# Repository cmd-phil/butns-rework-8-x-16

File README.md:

# Overview

128 button grid as a rework of jhbruhns 64 clone heavily based on previous work by [hugelton/btns](https://github.com/hugelton/Btns).

Uses a Rasperry Pi Pico Microcontroller, NeoPixel RGB LEDs (SK6812), cheap buttons and a 3d-printed case and button-overlay.
The tilt-sensor of the 8x8 version is not available: all usable GPIOs are needed for the 8x16 matrix.

## 16x8 specifics

| Item | Value |
|------|-------|
| PCB size | 190.44 mm x 99 mm, 2 layers |
| Rows `SW_ROW_1..8` | GPIO0..7 |
| Columns `SW_COL_1..7` | GPIO8..14 |
| Columns `SW_COL_8..15` | GPIO16, 17, 18, 19, 20, 21, 22, 26 |
| Column `SW_COL_16` | GPIO15 |
| LED data | GPIO28 via 74LVC1G17, one chain of 128 LEDs, row by row, 16 per row, starting top left |
| Free GPIO | GPIO27 |
| Mounting holes | 4 corners, 2 inner (M2.5) |

The firmware limits the estimated LED current to `MAX_LED_CURRENT_MA` (400 mA, see `firmware/src/firmware.cpp`).
One SK6812-EC20 draws up to 12 mA per colour channel plus about 1 mA idle, so 128 LEDs at full level exceed what a USB port and the 0.2 mm supply traces can deliver.
Hold the top-left key while plugging in for the default orientation, the bottom-right key for 180 degrees.

An alternative firmware in `firmware-iii/` runs monome iii Lua scripts with colour functions for the RGB LEDs and also has a monome serial mode. See `firmware-iii/README.md`.

Maximum LED brightness: hold the two top corner keys for one second. Then press any key, its column sets the maximum (column 1 = 1/16, column 16 = 100 %).
The selected column lights up at that brightness. The mode ends 3 seconds after the last key press and the value is stored in flash.
No key events are sent to the host while the mode is active.

# Building

It is highly recommended to order the PCB assembled from JLCPCB. That assembly will include everything other than the parts in the BOM.

## BOM

| Part                            | Quantity | Source                                                                                                                                                                                                                                                                                                                        | Required                      | 
|---------------------------------|----------|-------------------------------------------------------------------------------------------------------------------------------------------------------------------------------------------------------------------------------------------------------------------------------------------------------------------------------|-------------------------------|
| PCB with components             | 1        | JLCPCB, ordered with Gerber and Assembly files from latest release. Gerber: `butns-JLCPCB.zip`, BOM: `butns_bom_jlc.csv`, CPL: `butns_cpl_jlc.csv`.                                                                                                                                                                                                                                                            | yes                           | 
| Raspberry Pi Pico               | 1        | Original Raspberry Pi Pico, or [USB-C Variant](https://de.aliexpress.com/item/1005007393927221.html)                                                                                                                                                                                                                          | yes                           |   |
| M2.5x6 Button Head Screws       | 6        | [M2.5x6](https://www.aliexpress.com/item/32810852732.html)                                                                                                                                                                                                                                                                    | yes                           | 
| Case                        | 1        | 3d-printed (FDM). `case.stl` contains the top and bottom half. In the image, it is printed in black PLA, 0.2mm layerheight.                                                                                                                                                                                                   | yes                           | 
| Button Matrix                     | 1        | 3d-printed (FDM). Print `buttons.stl` with white PLA and 0.12mm layerheight and no infill, 2 wall lines, concentric top infill. These should guide the LEDs light well. Optional: Add `buttons-black-blockers.stl` while importing as a multi-material print and print those in black to block light from neighboring buttons | yes (black blockers optional) | 
| Button TPU Case Inlay         | 1        | 3d-printed (FDM). Print with TPU, perhaps in black. Will help against rattling of the buttons in the case.                                                                                                                                                                                                                    | no                            | 

## Assembly

Flash microcontroller with `firmware.uf2`. Solder MCU to PCB. Screw everything into the case. Done!

Hint: The cases Top half has one specific orientation where it fits nicely: The top-screw-posts of the top-half with the larger cutoaways go to the side opposite of the USB Connector.

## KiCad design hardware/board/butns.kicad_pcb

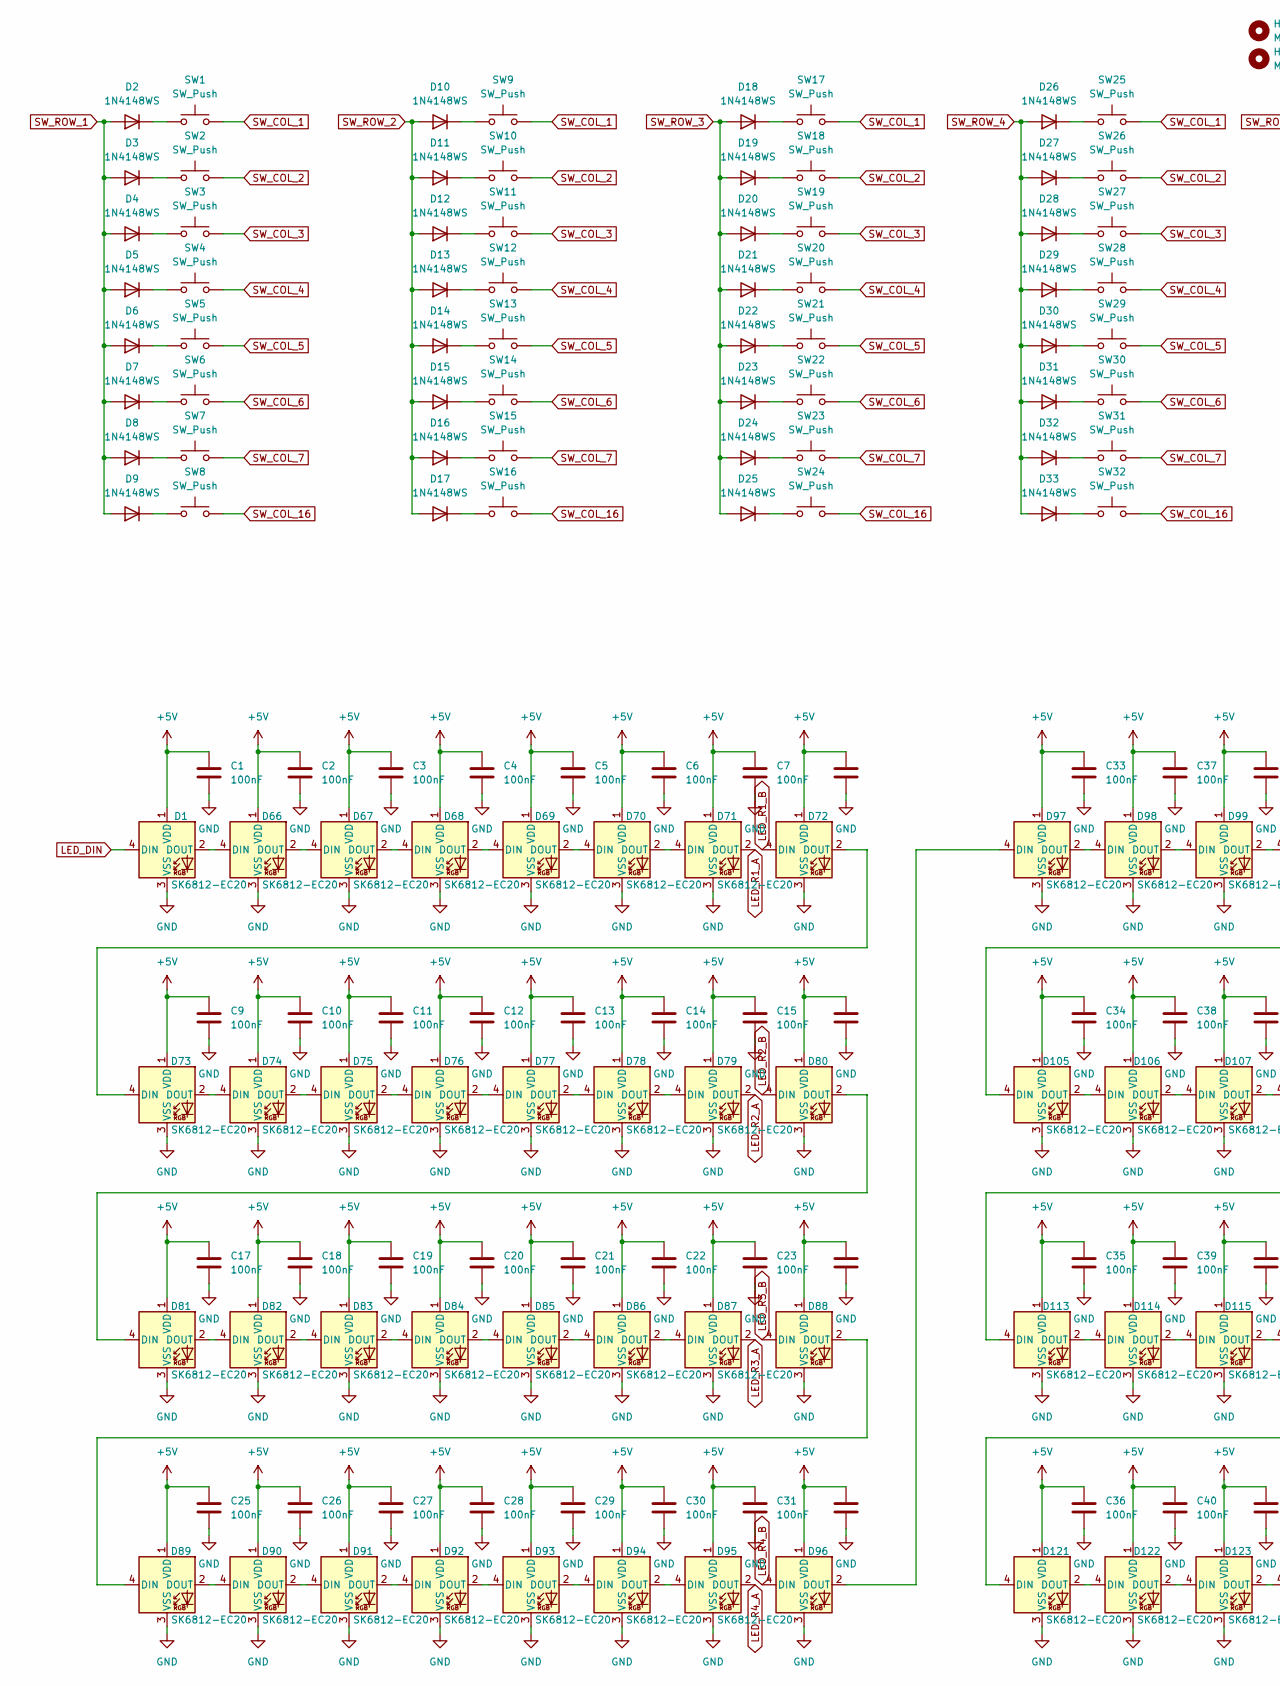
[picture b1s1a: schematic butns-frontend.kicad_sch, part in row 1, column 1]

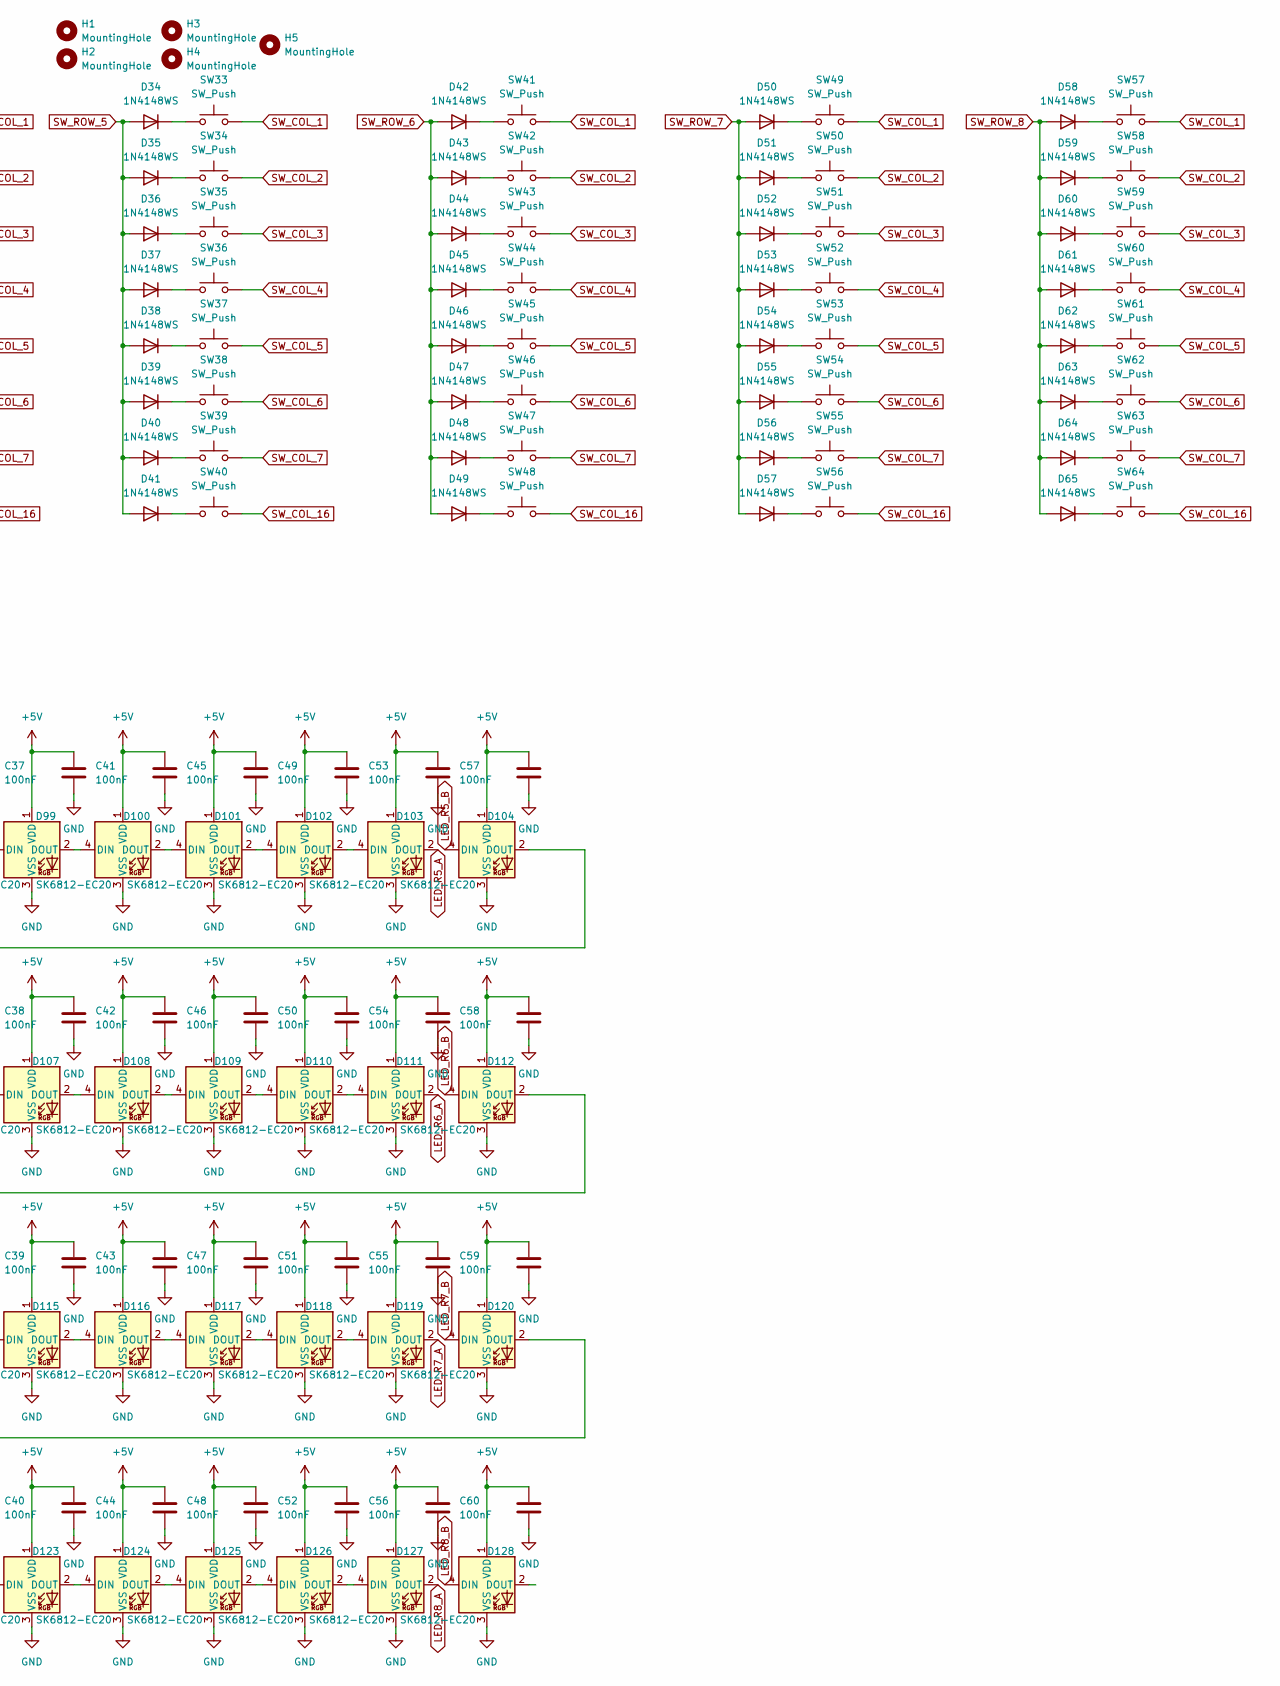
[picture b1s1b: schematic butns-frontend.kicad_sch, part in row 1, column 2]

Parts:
C1, C2, C3, C4, C5, C6, C7, C8, C9, C10, C11, C12, C13, C14, C15, C16, C17, C18, C19, C20, C21, C22, C23, C24, C25, C26, C27, C28, C29, C30, C31, C32, C33, C34, C35, C36, C37, C38, C39, C40, C41, C42, C43, C44, C45, C46, C47, C48, C49, C50, C51, C52, C53, C54, C55, C56, C57, C58, C59, C60, C61, C62, C63, C64: 100nF; C_0603_1608Metric; LCSC C14663
D1, D66, D67, D68, D69, D70, D71, D72, D73, D74, D75, D76, D77, D78, D79, D80, D81, D82, D83, D84, D85, D86, D87, D88, D89, D90, D91, D92, D93, D94, D95, D96, D97, D98, D99, D100, D101, D102, D103, D104, D105, D106, D107, D108, D109, D110, D111, D112, D113, D114, D115, D116, D117, D118, D119, D120, D121, D122, D123, D124, D125, D126, D127, D128: SK6812-EC20; LCSC C2909058
D2, D3, D4, D5, D6, D7, D8, D9, D10, D11, D12, D13, D14, D15, D16, D17, D18, D19, D20, D21, D22, D23, D24, D25, D26, D27, D28, D29, D30, D31, D32, D33, D34, D35, D36, D37, D38, D39, D40, D41, D42, D43, D44, D45, D46, D47, D48, D49, D50, D51, D52, D53, D54, D55, D56, D57, D58, D59, D60, D61, D62, D63, D64, D65: 1N4148WS; D_SOD-323; LCSC C2128
H1, H2, H3, H4, H5: MountingHole; MountingHole_2.7mm_M2.5
SW1, SW2, SW3, SW4, SW5, SW6, SW7, SW8, SW9, SW10, SW11, SW12, SW13, SW14, SW15, SW16, SW17, SW18, SW19, SW20, SW21, SW22, SW23, SW24, SW25, SW26, SW27, SW28, SW29, SW30, SW31, SW32, SW33, SW34, SW35, SW36, SW37, SW38, SW39, SW40, SW41, SW42, SW43, SW44, SW45, SW46, SW47, SW48, SW49, SW50, SW51, SW52, SW53, SW54, SW55, SW56, SW57, SW58, SW59, SW60, SW61, SW62, SW63, SW64: SW_Push; SW_Push_1P1T_XKB_TS-1187A; LCSC C318884

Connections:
+5V: C1.1, C2.1, C3.1, C4.1, C5.1, C6.1, C7.1, C8.1, C9.1, C10.1, C11.1, C12.1, C13.1, C14.1, C15.1, C16.1, C17.1, C18.1, C19.1, C20.1, C21.1, C22.1, C23.1, C24.1, C25.1, C26.1, C27.1, C28.1, C29.1, C30.1, C31.1, C32.1, C33.1, C34.1, C35.1, C36.1, C37.1, C38.1, C39.1, C40.1, C41.1, C42.1, C43.1, C44.1, C45.1, C46.1, C47.1, C48.1, C49.1, C50.1, C51.1, C52.1, C53.1, C54.1, C55.1, C56.1, C57.1, C58.1, C59.1, C60.1, C61.1, C62.1, C63.1, C64.1, D1.1 (VDD), D66.1 (VDD), D67.1 (VDD), D68.1 (VDD), D69.1 (VDD), D70.1 (VDD), D71.1 (VDD), D72.1 (VDD), D73.1 (VDD), D74.1 (VDD), D75.1 (VDD), D76.1 (VDD), D77.1 (VDD), D78.1 (VDD), D79.1 (VDD), D80.1 (VDD), D81.1 (VDD), D82.1 (VDD), D83.1 (VDD), D84.1 (VDD), D85.1 (VDD), D86.1 (VDD), D87.1 (VDD), D88.1 (VDD), D89.1 (VDD), D90.1 (VDD), D91.1 (VDD), D92.1 (VDD), D93.1 (VDD), D94.1 (VDD), D95.1 (VDD), D96.1 (VDD), D97.1 (VDD), D98.1 (VDD), D99.1 (VDD), D100.1 (VDD), D101.1 (VDD), D102.1 (VDD), D103.1 (VDD), D104.1 (VDD), D105.1 (VDD), D106.1 (VDD), D107.1 (VDD), D108.1 (VDD), D109.1 (VDD), D110.1 (VDD), D111.1 (VDD), D112.1 (VDD), D113.1 (VDD), D114.1 (VDD), D115.1 (VDD), D116.1 (VDD), D117.1 (VDD), D118.1 (VDD), D119.1 (VDD), D120.1 (VDD), D121.1 (VDD), D122.1 (VDD), D123.1 (VDD), D124.1 (VDD), D125.1 (VDD), D126.1 (VDD), D127.1 (VDD), D128.1 (VDD); also elsewhere on the board
GND: C1.2, C2.2, C3.2, C4.2, C5.2, C6.2, C7.2, C8.2, C9.2, C10.2, C11.2, C12.2, C13.2, C14.2, C15.2, C16.2, C17.2, C18.2, C19.2, C20.2, C21.2, C22.2, C23.2, C24.2, C25.2, C26.2, C27.2, C28.2, C29.2, C30.2, C31.2, C32.2, C33.2, C34.2, C35.2, C36.2, C37.2, C38.2, C39.2, C40.2, C41.2, C42.2, C43.2, C44.2, C45.2, C46.2, C47.2, C48.2, C49.2, C50.2, C51.2, C52.2, C53.2, C54.2, C55.2, C56.2, C57.2, C58.2, C59.2, C60.2, C61.2, C62.2, C63.2, C64.2, D1.3 (VSS), D66.3 (VSS), D67.3 (VSS), D68.3 (VSS), D69.3 (VSS), D70.3 (VSS), D71.3 (VSS), D72.3 (VSS), D73.3 (VSS), D74.3 (VSS), D75.3 (VSS), D76.3 (VSS), D77.3 (VSS), D78.3 (VSS), D79.3 (VSS), D80.3 (VSS), D81.3 (VSS), D82.3 (VSS), D83.3 (VSS), D84.3 (VSS), D85.3 (VSS), D86.3 (VSS), D87.3 (VSS), D88.3 (VSS), D89.3 (VSS), D90.3 (VSS), D91.3 (VSS), D92.3 (VSS), D93.3 (VSS), D94.3 (VSS), D95.3 (VSS), D96.3 (VSS), D97.3 (VSS), D98.3 (VSS), D99.3 (VSS), D100.3 (VSS), D101.3 (VSS), D102.3 (VSS), D103.3 (VSS), D104.3 (VSS), D105.3 (VSS), D106.3 (VSS), D107.3 (VSS), D108.3 (VSS), D109.3 (VSS), D110.3 (VSS), D111.3 (VSS), D112.3 (VSS), D113.3 (VSS), D114.3 (VSS), D115.3 (VSS), D116.3 (VSS), D117.3 (VSS), D118.3 (VSS), D119.3 (VSS), D120.3 (VSS), D121.3 (VSS), D122.3 (VSS), D123.3 (VSS), D124.3 (VSS), D125.3 (VSS), D126.3 (VSS), D127.3 (VSS), D128.3 (VSS); also elsewhere on the board
LED_DIN: D1.4 (DIN); also elsewhere on the board
LED_R1_A: D71.2 (DOUT); also elsewhere on the board
LED_R1_B: D72.4 (DIN); also elsewhere on the board
LED_R2_A: D79.2 (DOUT); also elsewhere on the board
LED_R2_B: D80.4 (DIN); also elsewhere on the board
LED_R3_A: D87.2 (DOUT); also elsewhere on the board
LED_R3_B: D88.4 (DIN); also elsewhere on the board
LED_R4_A: D95.2 (DOUT); also elsewhere on the board
LED_R4_B: D96.4 (DIN); also elsewhere on the board
LED_R5_A: D103.2 (DOUT); also elsewhere on the board
LED_R5_B: D104.4 (DIN); also elsewhere on the board
LED_R6_A: D111.2 (DOUT); also elsewhere on the board
LED_R6_B: D112.4 (DIN); also elsewhere on the board
LED_R7_A: D119.2 (DOUT); also elsewhere on the board
LED_R7_B: D120.4 (DIN); also elsewhere on the board
LED_R8_A: D127.2 (DOUT); also elsewhere on the board
LED_R8_B: D128.4 (DIN); also elsewhere on the board
unnamed: D1.2 (DOUT), D66.4 (DIN)
unnamed: D2.1 (K), SW1.1
unnamed: D3.1 (K), SW2.1
unnamed: D4.1 (K), SW3.1
unnamed: D5.1 (K), SW4.1
unnamed: D6.1 (K), SW5.1
unnamed: D7.1 (K), SW6.1
unnamed: D8.1 (K), SW7.1
unnamed: D9.1 (K), SW8.1
unnamed: D10.1 (K), SW9.1
unnamed: D11.1 (K), SW10.1
unnamed: D12.1 (K), SW11.1
unnamed: D13.1 (K), SW12.1
unnamed: D14.1 (K), SW13.1
unnamed: D15.1 (K), SW14.1
unnamed: D16.1 (K), SW15.1
unnamed: D17.1 (K), SW16.1
unnamed: D18.1 (K), SW17.1
unnamed: D19.1 (K), SW18.1
unnamed: D20.1 (K), SW19.1
unnamed: D21.1 (K), SW20.1
unnamed: D22.1 (K), SW21.1
unnamed: D23.1 (K), SW22.1
unnamed: D24.1 (K), SW23.1
unnamed: D25.1 (K), SW24.1
unnamed: D26.1 (K), SW25.1
unnamed: D27.1 (K), SW26.1
unnamed: D28.1 (K), SW27.1
unnamed: D29.1 (K), SW28.1
unnamed: D30.1 (K), SW29.1
unnamed: D31.1 (K), SW30.1
unnamed: D32.1 (K), SW31.1
unnamed: D33.1 (K), SW32.1
unnamed: D34.1 (K), SW33.1
unnamed: D35.1 (K), SW34.1
unnamed: D36.1 (K), SW35.1
unnamed: D37.1 (K), SW36.1
unnamed: D38.1 (K), SW37.1
unnamed: D39.1 (K), SW38.1
unnamed: D40.1 (K), SW39.1
unnamed: D41.1 (K), SW40.1
unnamed: D42.1 (K), SW41.1
unnamed: D43.1 (K), SW42.1
unnamed: D44.1 (K), SW43.1
unnamed: D45.1 (K), SW44.1
unnamed: D46.1 (K), SW45.1
unnamed: D47.1 (K), SW46.1
unnamed: D48.1 (K), SW47.1
unnamed: D49.1 (K), SW48.1
unnamed: D50.1 (K), SW49.1
unnamed: D51.1 (K), SW50.1
unnamed: D52.1 (K), SW51.1
unnamed: D53.1 (K), SW52.1
unnamed: D54.1 (K), SW53.1
unnamed: D55.1 (K), SW54.1
unnamed: D56.1 (K), SW55.1
unnamed: D57.1 (K), SW56.1
unnamed: D58.1 (K), SW57.1
unnamed: D59.1 (K), SW58.1
unnamed: D60.1 (K), SW59.1
unnamed: D61.1 (K), SW60.1
unnamed: D62.1 (K), SW61.1
unnamed: D63.1 (K), SW62.1
unnamed: D64.1 (K), SW63.1
unnamed: D65.1 (K), SW64.1
unnamed: D66.2 (DOUT), D67.4 (DIN)
unnamed: D67.2 (DOUT), D68.4 (DIN)
unnamed: D68.2 (DOUT), D69.4 (DIN)
unnamed: D69.2 (DOUT), D70.4 (DIN)
unnamed: D70.2 (DOUT), D71.4 (DIN)
unnamed: D72.2 (DOUT), D73.4 (DIN)
unnamed: D73.2 (DOUT), D74.4 (DIN)
unnamed: D74.2 (DOUT), D75.4 (DIN)
unnamed: D75.2 (DOUT), D76.4 (DIN)
unnamed: D76.2 (DOUT), D77.4 (DIN)
unnamed: D77.2 (DOUT), D78.4 (DIN)
unnamed: D78.2 (DOUT), D79.4 (DIN)
unnamed: D80.2 (DOUT), D81.4 (DIN)
unnamed: D81.2 (DOUT), D82.4 (DIN)
unnamed: D82.2 (DOUT), D83.4 (DIN)
unnamed: D83.2 (DOUT), D84.4 (DIN)
unnamed: D84.2 (DOUT), D85.4 (DIN)
unnamed: D85.2 (DOUT), D86.4 (DIN)
unnamed: D86.2 (DOUT), D87.4 (DIN)
unnamed: D88.2 (DOUT), D89.4 (DIN)
unnamed: D89.2 (DOUT), D90.4 (DIN)
unnamed: D90.2 (DOUT), D91.4 (DIN)
unnamed: D91.2 (DOUT), D92.4 (DIN)
unnamed: D92.2 (DOUT), D93.4 (DIN)
unnamed: D93.2 (DOUT), D94.4 (DIN)
unnamed: D94.2 (DOUT), D95.4 (DIN)
unnamed: D96.2 (DOUT), D97.4 (DIN)
unnamed: D97.2 (DOUT), D98.4 (DIN)
unnamed: D98.2 (DOUT), D99.4 (DIN)
unnamed: D99.2 (DOUT), D100.4 (DIN)
unnamed: D100.2 (DOUT), D101.4 (DIN)
unnamed: D101.2 (DOUT), D102.4 (DIN)
unnamed: D102.2 (DOUT), D103.4 (DIN)
unnamed: D104.2 (DOUT), D105.4 (DIN)
unnamed: D105.2 (DOUT), D106.4 (DIN)
unnamed: D106.2 (DOUT), D107.4 (DIN)
unnamed: D107.2 (DOUT), D108.4 (DIN)
unnamed: D108.2 (DOUT), D109.4 (DIN)
unnamed: D109.2 (DOUT), D110.4 (DIN)
unnamed: D110.2 (DOUT), D111.4 (DIN)
unnamed: D112.2 (DOUT), D113.4 (DIN)
unnamed: D113.2 (DOUT), D114.4 (DIN)
unnamed: D114.2 (DOUT), D115.4 (DIN)
unnamed: D115.2 (DOUT), D116.4 (DIN)
unnamed: D116.2 (DOUT), D117.4 (DIN)
unnamed: D117.2 (DOUT), D118.4 (DIN)
unnamed: D118.2 (DOUT), D119.4 (DIN)
unnamed: D120.2 (DOUT), D121.4 (DIN)
unnamed: D121.2 (DOUT), D122.4 (DIN)
unnamed: D122.2 (DOUT), D123.4 (DIN)
unnamed: D123.2 (DOUT), D124.4 (DIN)
unnamed: D124.2 (DOUT), D125.4 (DIN)
unnamed: D125.2 (DOUT), D126.4 (DIN)
unnamed: D126.2 (DOUT), D127.4 (DIN)
SW_COL_1: SW1.2, SW9.2, SW17.2, SW25.2, SW33.2, SW41.2, SW49.2, SW57.2; also elsewhere on the board
SW_COL_2: SW2.2, SW10.2, SW18.2, SW26.2, SW34.2, SW42.2, SW50.2, SW58.2; also elsewhere on the board
SW_COL_3: SW3.2, SW11.2, SW19.2, SW27.2, SW35.2, SW43.2, SW51.2, SW59.2; also elsewhere on the board
SW_COL_4: SW4.2, SW12.2, SW20.2, SW28.2, SW36.2, SW44.2, SW52.2, SW60.2; also elsewhere on the board
SW_COL_5: SW5.2, SW13.2, SW21.2, SW29.2, SW37.2, SW45.2, SW53.2, SW61.2; also elsewhere on the board
SW_COL_6: SW6.2, SW14.2, SW22.2, SW30.2, SW38.2, SW46.2, SW54.2, SW62.2; also elsewhere on the board
SW_COL_7: SW7.2, SW15.2, SW23.2, SW31.2, SW39.2, SW47.2, SW55.2, SW63.2; also elsewhere on the board
SW_COL_16: SW8.2, SW16.2, SW24.2, SW32.2, SW40.2, SW48.2, SW56.2, SW64.2; also elsewhere on the board
SW_ROW_1: D2.2 (A), D3.2 (A), D4.2 (A), D5.2 (A), D6.2 (A), D7.2 (A), D8.2 (A), D9.2 (A); also elsewhere on the board
SW_ROW_2: D10.2 (A), D11.2 (A), D12.2 (A), D13.2 (A), D14.2 (A), D15.2 (A), D16.2 (A), D17.2 (A); also elsewhere on the board
SW_ROW_3: D18.2 (A), D19.2 (A), D20.2 (A), D21.2 (A), D22.2 (A), D23.2 (A), D24.2 (A), D25.2 (A); also elsewhere on the board
SW_ROW_4: D26.2 (A), D27.2 (A), D28.2 (A), D29.2 (A), D30.2 (A), D31.2 (A), D32.2 (A), D33.2 (A); also elsewhere on the board
SW_ROW_5: D34.2 (A), D35.2 (A), D36.2 (A), D37.2 (A), D38.2 (A), D39.2 (A), D40.2 (A), D41.2 (A); also elsewhere on the board
SW_ROW_6: D42.2 (A), D43.2 (A), D44.2 (A), D45.2 (A), D46.2 (A), D47.2 (A), D48.2 (A), D49.2 (A); also elsewhere on the board
SW_ROW_7: D50.2 (A), D51.2 (A), D52.2 (A), D53.2 (A), D54.2 (A), D55.2 (A), D56.2 (A), D57.2 (A); also elsewhere on the board
SW_ROW_8: D58.2 (A), D59.2 (A), D60.2 (A), D61.2 (A), D62.2 (A), D63.2 (A), D64.2 (A), D65.2 (A); also elsewhere on the board

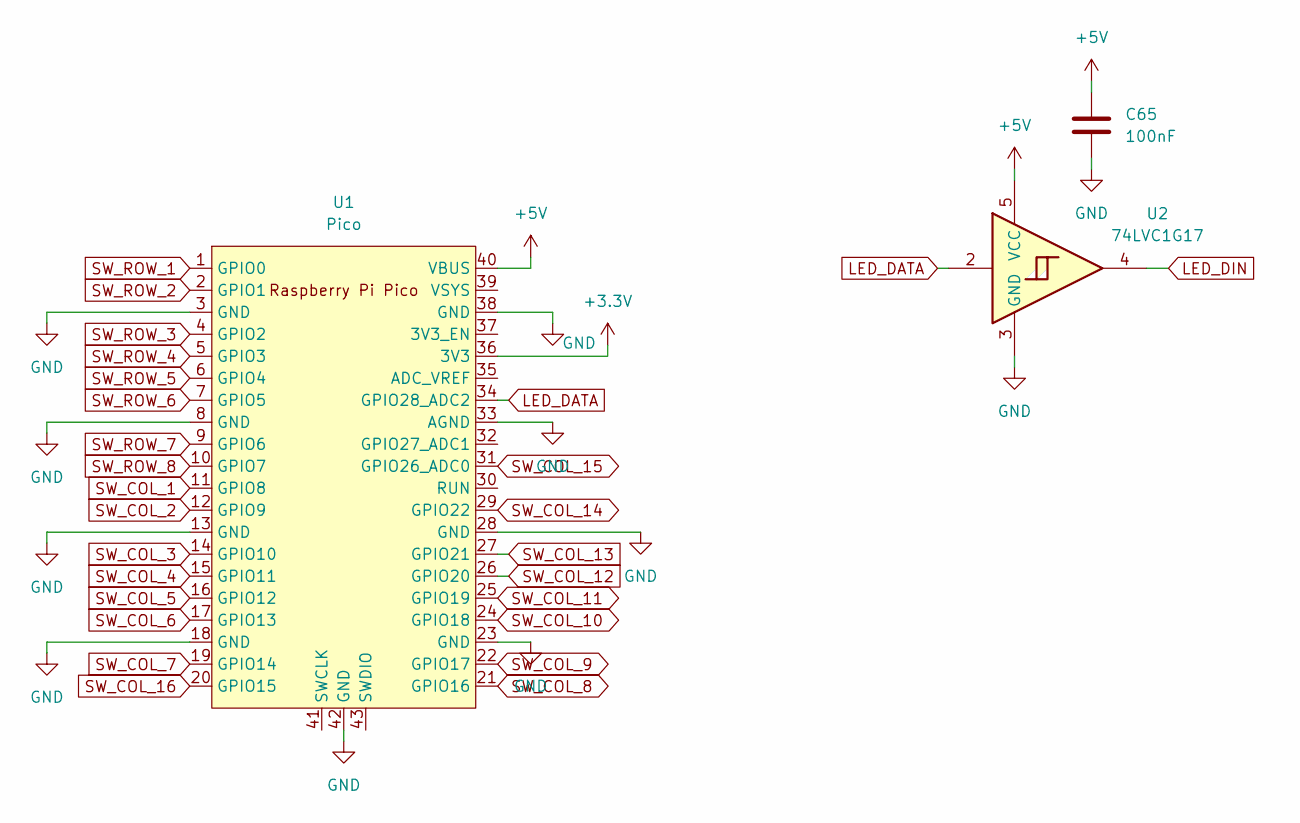
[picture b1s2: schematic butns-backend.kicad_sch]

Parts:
C65: 100nF; C_0603_1608Metric
U1: Pico; RPi_Pico_SMD_TH
U2: 74LVC1G17; SOT-23-5_HandSoldering

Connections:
+3.3V: U1.36 (3V3)
+5V: C65.1, U1.40 (VBUS), U2.5 (VCC); also elsewhere on the board
GND: C65.2, U1.3 (GND), U1.8 (GND), U1.13 (GND), U1.18 (GND), U1.23 (GND), U1.28 (GND), U1.33 (AGND), U1.38 (GND), U1.42 (GND), U2.3 (GND); also elsewhere on the board
LED_DATA: U1.34 (GPIO28_ADC2), U2.2
LED_DIN: U2.4; also elsewhere on the board
SW_COL_1: U1.11 (GPIO8); also elsewhere on the board
SW_COL_2: U1.12 (GPIO9); also elsewhere on the board
SW_COL_3: U1.14 (GPIO10); also elsewhere on the board
SW_COL_4: U1.15 (GPIO11); also elsewhere on the board
SW_COL_5: U1.16 (GPIO12); also elsewhere on the board
SW_COL_6: U1.17 (GPIO13); also elsewhere on the board
SW_COL_7: U1.19 (GPIO14); also elsewhere on the board
SW_COL_8: U1.21 (GPIO16); also elsewhere on the board
SW_COL_9: U1.22 (GPIO17); also elsewhere on the board
SW_COL_10: U1.24 (GPIO18); also elsewhere on the board
SW_COL_11: U1.25 (GPIO19); also elsewhere on the board
SW_COL_12: U1.26 (GPIO20); also elsewhere on the board
SW_COL_13: U1.27 (GPIO21); also elsewhere on the board
SW_COL_14: U1.29 (GPIO22); also elsewhere on the board
SW_COL_15: U1.31 (GPIO26_ADC0); also elsewhere on the board
SW_COL_16: U1.20 (GPIO15); also elsewhere on the board
SW_ROW_1: U1.1 (GPIO0); also elsewhere on the board
SW_ROW_2: U1.2 (GPIO1); also elsewhere on the board
SW_ROW_3: U1.4 (GPIO2); also elsewhere on the board
SW_ROW_4: U1.5 (GPIO3); also elsewhere on the board
SW_ROW_5: U1.6 (GPIO4); also elsewhere on the board
SW_ROW_6: U1.7 (GPIO5); also elsewhere on the board
SW_ROW_7: U1.9 (GPIO6); also elsewhere on the board
SW_ROW_8: U1.10 (GPIO7); also elsewhere on the board
